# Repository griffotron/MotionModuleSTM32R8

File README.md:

# Introduction 
This repository contains the PCB design files and source code for the STM32 based Motion Module used in my Mechanical Display.

The Motion Module uses an STM32F103R8 microcontroller to run 14 Trinamic TMC2209 stepper drivers. It recieves motor movement commands via CAN Bus from the ESP32 based Motion Controller. Please see the related repos for the [ESP32 Controller](https://github.com/griffotron/MotionControllerESP32) and [CAD Designs](https://github.com/griffotron/MechanicalDisplayCAD).

# Build Video
Click below to watch the full build video on YouTube

# Getting Started

## PCB
You'll need at least KiCad 8 to view and modify the PCB design files. The `PCB/production` folder contains files suitable for production with JLC PCB, including a zip containing the Gerbers for fabrication and `bom.csv` and `positions.csv` for SMT assembly. The `bom.csv` uses components from LCSC.com. If any components are no longer be available/out of stock you'll need to select an alternative.

## Code
The code uses PlatformIO (I used the VSCode plugin) and the Arduino framework.

CAN Bus library is from https://github.com/pazi88/CANBus

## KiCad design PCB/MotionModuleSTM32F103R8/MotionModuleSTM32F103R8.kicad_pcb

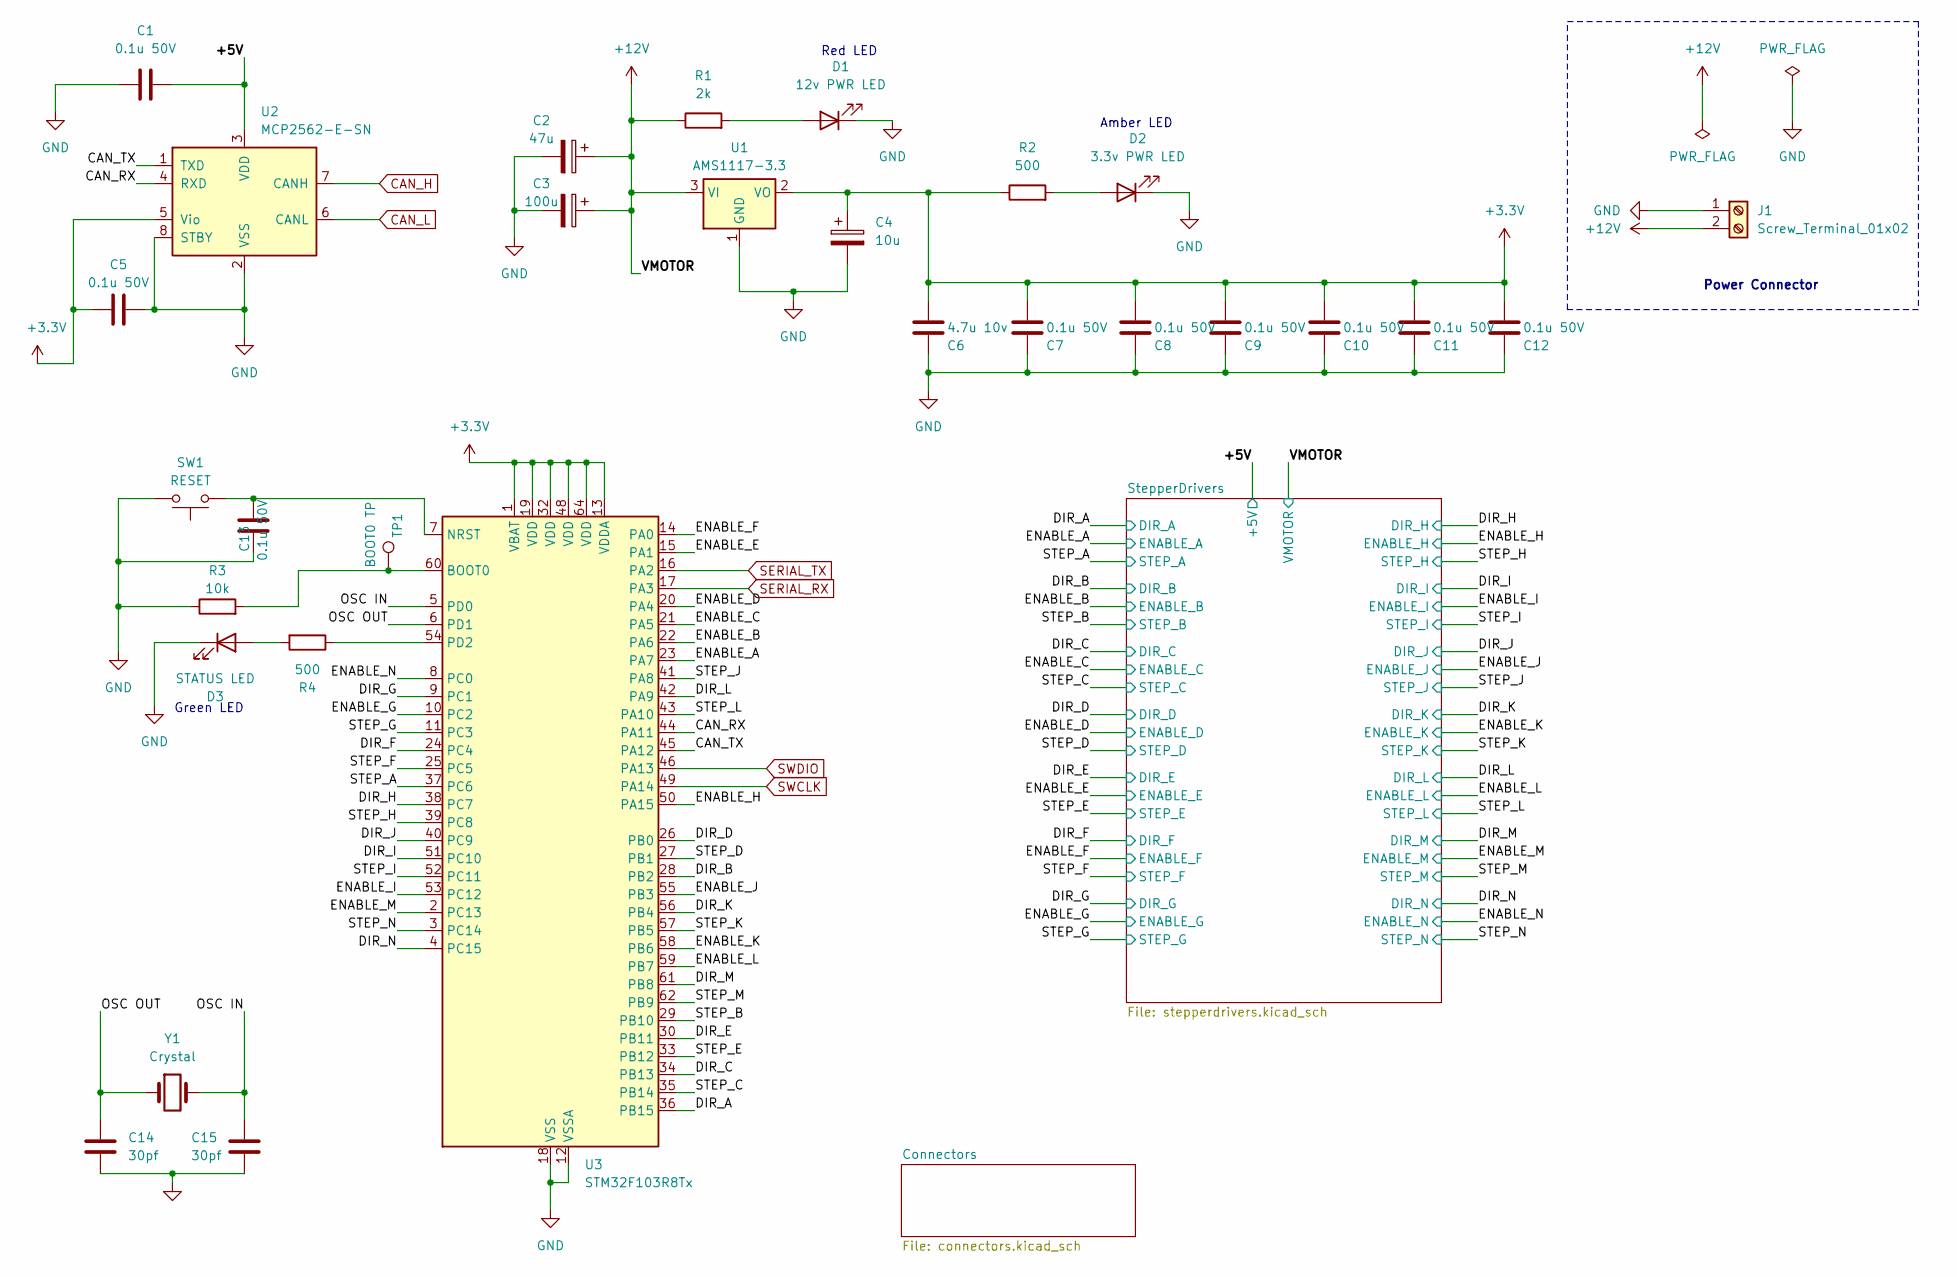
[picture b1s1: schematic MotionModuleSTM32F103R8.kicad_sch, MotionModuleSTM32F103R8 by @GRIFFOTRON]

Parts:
C1, C5, C7, C8, C9, C10, C11, C12, C13: 0.1u 50V; C_0603_1608Metric; MPN CC0603KRX7R9BB104; LCSC C14663
C2: 47u; CP_Elec_5x5.4; MPN RST47UF25V035; LCSC C4747958
C3: 100u; CP_Elec_6.3x4.9; MPN SPT1EM101E05TRVZC; LCSC C22395169
C4: 10u; CP_Elec_4x5.7; MPN FZ10UF25V90RV0144; DigiKey 732-6401-1-ND (Poly)
C6: 4.7u 10v; C_0603_1608Metric; MPN CL10A475KO8NNNC; LCSC C19666
C14, C15: 30pf; C_0603_1608Metric; MPN 0603CG300J500NT; LCSC C1658
D1: 12v PWR LED; LED_0603_1608Metric; MPN A-SP192YR6C-A02-4T; DigiKey 732-4978-1-ND
D2: 3.3v PWR LED; LED_0603_1608Metric; MPN A-SP192GS1C-A01-4T; DigiKey 732-150060AS75000CT-ND
D3: STATUS LED; LED_0603_1608Metric; MPN A-SP192DGHC-C01-4T; DigiKey 732-4971-1-ND
J1: Screw_Terminal_01x02; PinHeader_1x02_P2.54mm_Vertical
R1: 2k; R_0603_1608Metric; MPN 0603WAF2001T5E; LCSC C22975
R2, R4: 500; R_0603_1608Metric; MPN 0603WAF5100T5E; LCSC C23193
R3: 10k; R_0603_1608Metric; MPN 0603WAF1002T5E; LCSC C25804
SW1: RESET; SW_Tactile_SPST_NO_Straight_CK_PTS636Sx25SMTRLFS; MPN PTS636SK25SMTRLFS; LCSC C2689642
TP1: BOOT0 TP; TestPoint_Pad_D2.0mm
U1: AMS1117-3.3; SOT-223-3_TabPin2; MPN AMS1117-3.3; LCSC C5250992
U2: MCP2562-E-SN; SOIC-8_3.9x4.9mm_P1.27mm; MPN MCP2562T-E/SN; LCSC C191417
U3: STM32F103R8Tx; LQFP-64_10x10mm_P0.5mm; MPN STM32F103R8T6; LCSC C46034
Y1: Crystal; Crystal_SMD_5032-2Pin_5.0x3.2mm; MPN X50328MSB2GI; LCSC C115962

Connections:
+3.3V: C4.1, C5.2, C6.1, C7.1, C8.1, C9.1, C10.1, C11.1, C12.1, R2.1, U1.2 (VO), U2.5 (Vio), U3.1 (VBAT), U3.13 (VDDA), U3.19 (VDD), U3.32 (VDD), U3.48 (VDD), U3.64 (VDD)
+12V: C2.1, C3.1, J1.2, R1.1, U1.3 (VI); also elsewhere on the board
/+5V: C1.1, U2.3 (VDD); also elsewhere on the board
/CAN_RX: U2.4 (RXD), U3.44 (PA11)
/CAN_TX: U2.1 (TXD), U3.45 (PA12)
/DIR_A: U3.36 (PB15); also elsewhere on the board
/DIR_B: U3.28 (PB2); also elsewhere on the board
/DIR_C: U3.34 (PB13); also elsewhere on the board
/DIR_D: U3.26 (PB0); also elsewhere on the board
/DIR_E: U3.30 (PB11); also elsewhere on the board
/DIR_F: U3.24 (PC4); also elsewhere on the board
/DIR_G: U3.9 (PC1); also elsewhere on the board
/DIR_H: U3.38 (PC7); also elsewhere on the board
/DIR_I: U3.51 (PC10); also elsewhere on the board
/DIR_J: U3.40 (PC9); also elsewhere on the board
/DIR_K: U3.56 (PB4); also elsewhere on the board
/DIR_L: U3.42 (PA9); also elsewhere on the board
/DIR_M: U3.61 (PB8); also elsewhere on the board
/DIR_N: U3.4 (PC15); also elsewhere on the board
/ENABLE_A: U3.23 (PA7); also elsewhere on the board
/ENABLE_B: U3.22 (PA6); also elsewhere on the board
/ENABLE_C: U3.21 (PA5); also elsewhere on the board
/ENABLE_D: U3.20 (PA4); also elsewhere on the board
/ENABLE_E: U3.15 (PA1); also elsewhere on the board
/ENABLE_F: U3.14 (PA0); also elsewhere on the board
/ENABLE_G: U3.10 (PC2); also elsewhere on the board
/ENABLE_H: U3.50 (PA15); also elsewhere on the board
/ENABLE_I: U3.53 (PC12); also elsewhere on the board
/ENABLE_J: U3.55 (PB3); also elsewhere on the board
/ENABLE_K: U3.58 (PB6); also elsewhere on the board
/ENABLE_L: U3.59 (PB7); also elsewhere on the board
/ENABLE_M: U3.2 (PC13); also elsewhere on the board
/ENABLE_N: U3.8 (PC0); also elsewhere on the board
/OSC IN: C15.1, U3.5 (PD0), Y1.2
/OSC OUT: C14.2, U3.6 (PD1), Y1.1
/STEP_A: U3.37 (PC6); also elsewhere on the board
/STEP_B: U3.29 (PB10); also elsewhere on the board
/STEP_C: U3.35 (PB14); also elsewhere on the board
/STEP_D: U3.27 (PB1); also elsewhere on the board
/STEP_E: U3.33 (PB12); also elsewhere on the board
/STEP_F: U3.25 (PC5); also elsewhere on the board
/STEP_G: U3.11 (PC3); also elsewhere on the board
/STEP_H: U3.39 (PC8); also elsewhere on the board
/STEP_I: U3.52 (PC11); also elsewhere on the board
/STEP_J: U3.41 (PA8); also elsewhere on the board
/STEP_K: U3.57 (PB5); also elsewhere on the board
/STEP_L: U3.43 (PA10); also elsewhere on the board
/STEP_M: U3.62 (PB9); also elsewhere on the board
/STEP_N: U3.3 (PC14); also elsewhere on the board
CAN_H: U2.7 (CANH); also elsewhere on the board
CAN_L: U2.6 (CANL); also elsewhere on the board
GND: C1.2, C2.2, C3.2, C4.2, C5.1, C6.2, C7.2, C8.2, C9.2, C10.2, C11.2, C12.2, C13.2, C14.1, C15.2, D1.1 (K), D2.1 (K), D3.1 (K), J1.1, R3.1, SW1.2, U1.1 (GND), U2.2 (VSS), U2.8 (STBY), U3.12 (VSSA), U3.18 (VSS), U3.31 (VSS), U3.47 (VSS), U3.63 (VSS); also elsewhere on the board
unnamed: D1.2 (A), R1.2
unnamed: D2.2 (A), R2.2
unnamed: D3.2 (A), R4.2
unnamed: R3.2, TP1.1, U3.60 (BOOT0)
unnamed: C13.1, SW1.1, U3.7 (NRST)
unnamed: R4.1, U3.54 (PD2)
SERIAL_RX: U3.17 (PA3); also elsewhere on the board
SERIAL_TX: U3.16 (PA2); also elsewhere on the board
SWCLK: U3.49 (PA14); also elsewhere on the board
SWDIO: U3.46 (PA13); also elsewhere on the board

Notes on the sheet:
Green LED
Power Connector
Amber LED
Red LED

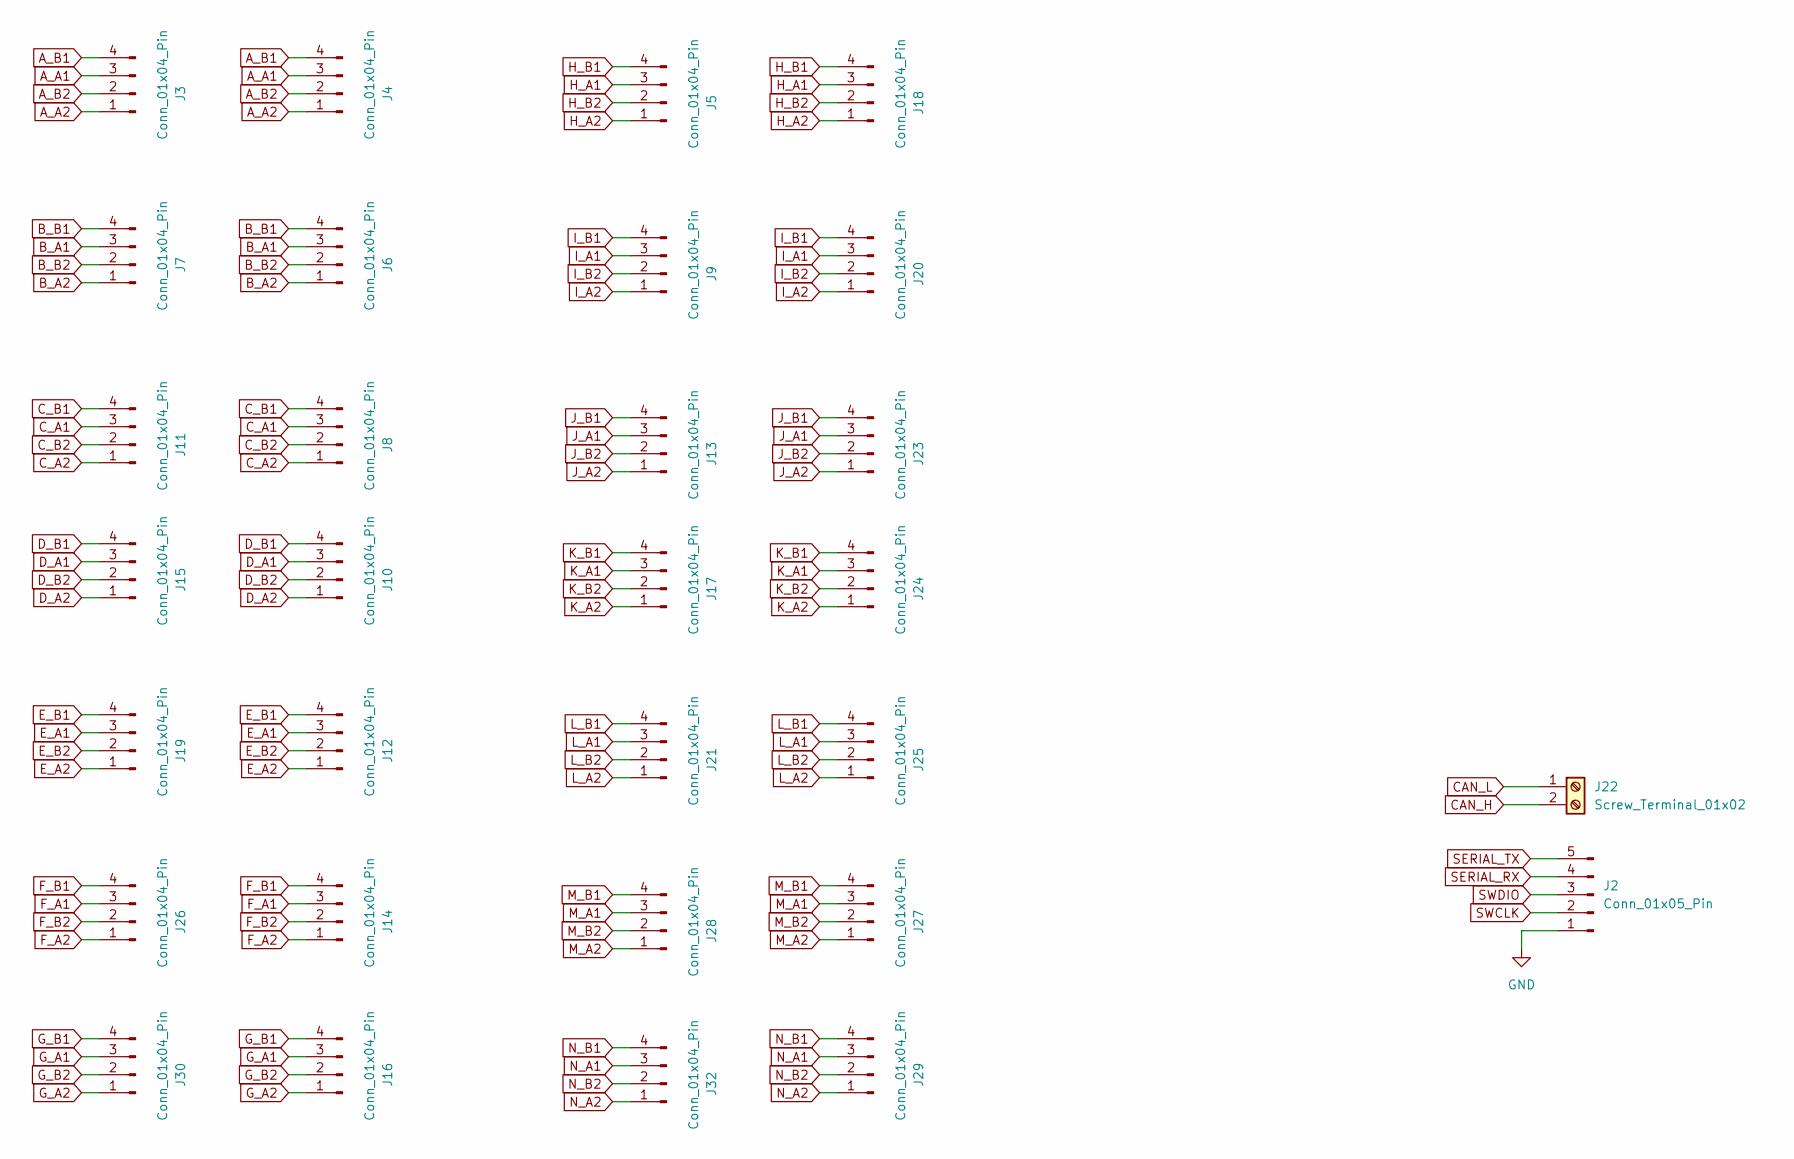
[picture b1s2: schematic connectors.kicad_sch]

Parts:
J2: Conn_01x05_Pin; PinHeader_1x05_P2.54mm_Vertical
J3, J5, J7, J9, J11, J13, J15, J17, J19, J21, J26, J28, J30, J32: Conn_01x04_Pin; JST_PH_B4B-PH-K_1x04_P2.00mm_Vertical; MPN B4B-PH-K-S(LF)(SN); LCSC C131334
J4, J6, J8, J10, J12, J14, J16, J18, J20, J23, J24, J25, J27, J29: Conn_01x04_Pin; PinHeader_1x04_P2.54mm_Vertical
J22: Screw_Terminal_01x02; PinHeader_1x02_P2.54mm_Vertical

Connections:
A_A1: J3.3, J4.3; also elsewhere on the board
A_A2: J3.1, J4.1; also elsewhere on the board
A_B1: J3.4, J4.4; also elsewhere on the board
A_B2: J3.2, J4.2; also elsewhere on the board
B_A1: J6.3, J7.3; also elsewhere on the board
B_A2: J6.1, J7.1; also elsewhere on the board
B_B1: J6.4, J7.4; also elsewhere on the board
B_B2: J6.2, J7.2; also elsewhere on the board
CAN_H: J22.2; also elsewhere on the board
CAN_L: J22.1; also elsewhere on the board
C_A1: J8.3, J11.3; also elsewhere on the board
C_A2: J8.1, J11.1; also elsewhere on the board
C_B1: J8.4, J11.4; also elsewhere on the board
C_B2: J8.2, J11.2; also elsewhere on the board
D_A1: J10.3, J15.3; also elsewhere on the board
D_A2: J10.1, J15.1; also elsewhere on the board
D_B1: J10.4, J15.4; also elsewhere on the board
D_B2: J10.2, J15.2; also elsewhere on the board
E_A1: J12.3, J19.3; also elsewhere on the board
E_A2: J12.1, J19.1; also elsewhere on the board
E_B1: J12.4, J19.4; also elsewhere on the board
E_B2: J12.2, J19.2; also elsewhere on the board
F_A1: J14.3, J26.3; also elsewhere on the board
F_A2: J14.1, J26.1; also elsewhere on the board
F_B1: J14.4, J26.4; also elsewhere on the board
F_B2: J14.2, J26.2; also elsewhere on the board
GND: J2.1; also elsewhere on the board
G_A1: J16.3, J30.3; also elsewhere on the board
G_A2: J16.1, J30.1; also elsewhere on the board
G_B1: J16.4, J30.4; also elsewhere on the board
G_B2: J16.2, J30.2; also elsewhere on the board
H_A1: J5.3, J18.3; also elsewhere on the board
H_A2: J5.1, J18.1; also elsewhere on the board
H_B1: J5.4, J18.4; also elsewhere on the board
H_B2: J5.2, J18.2; also elsewhere on the board
I_A1: J9.3, J20.3; also elsewhere on the board
I_A2: J9.1, J20.1; also elsewhere on the board
I_B1: J9.4, J20.4; also elsewhere on the board
I_B2: J9.2, J20.2; also elsewhere on the board
J_A1: J13.3, J23.3; also elsewhere on the board
J_A2: J13.1, J23.1; also elsewhere on the board
J_B1: J13.4, J23.4; also elsewhere on the board
J_B2: J13.2, J23.2; also elsewhere on the board
K_A1: J17.3, J24.3; also elsewhere on the board
K_A2: J17.1, J24.1; also elsewhere on the board
K_B1: J17.4, J24.4; also elsewhere on the board
K_B2: J17.2, J24.2; also elsewhere on the board
L_A1: J21.3, J25.3; also elsewhere on the board
L_A2: J21.1, J25.1; also elsewhere on the board
L_B1: J21.4, J25.4; also elsewhere on the board
L_B2: J21.2, J25.2; also elsewhere on the board
M_A1: J27.3, J28.3; also elsewhere on the board
M_A2: J27.1, J28.1; also elsewhere on the board
M_B1: J27.4, J28.4; also elsewhere on the board
M_B2: J27.2, J28.2; also elsewhere on the board
N_A1: J29.3, J32.3; also elsewhere on the board
N_A2: J29.1, J32.1; also elsewhere on the board
N_B1: J29.4, J32.4; also elsewhere on the board
N_B2: J29.2, J32.2; also elsewhere on the board
SERIAL_RX: J2.4; also elsewhere on the board
SERIAL_TX: J2.5; also elsewhere on the board
SWCLK: J2.2; also elsewhere on the board
SWDIO: J2.3; also elsewhere on the board

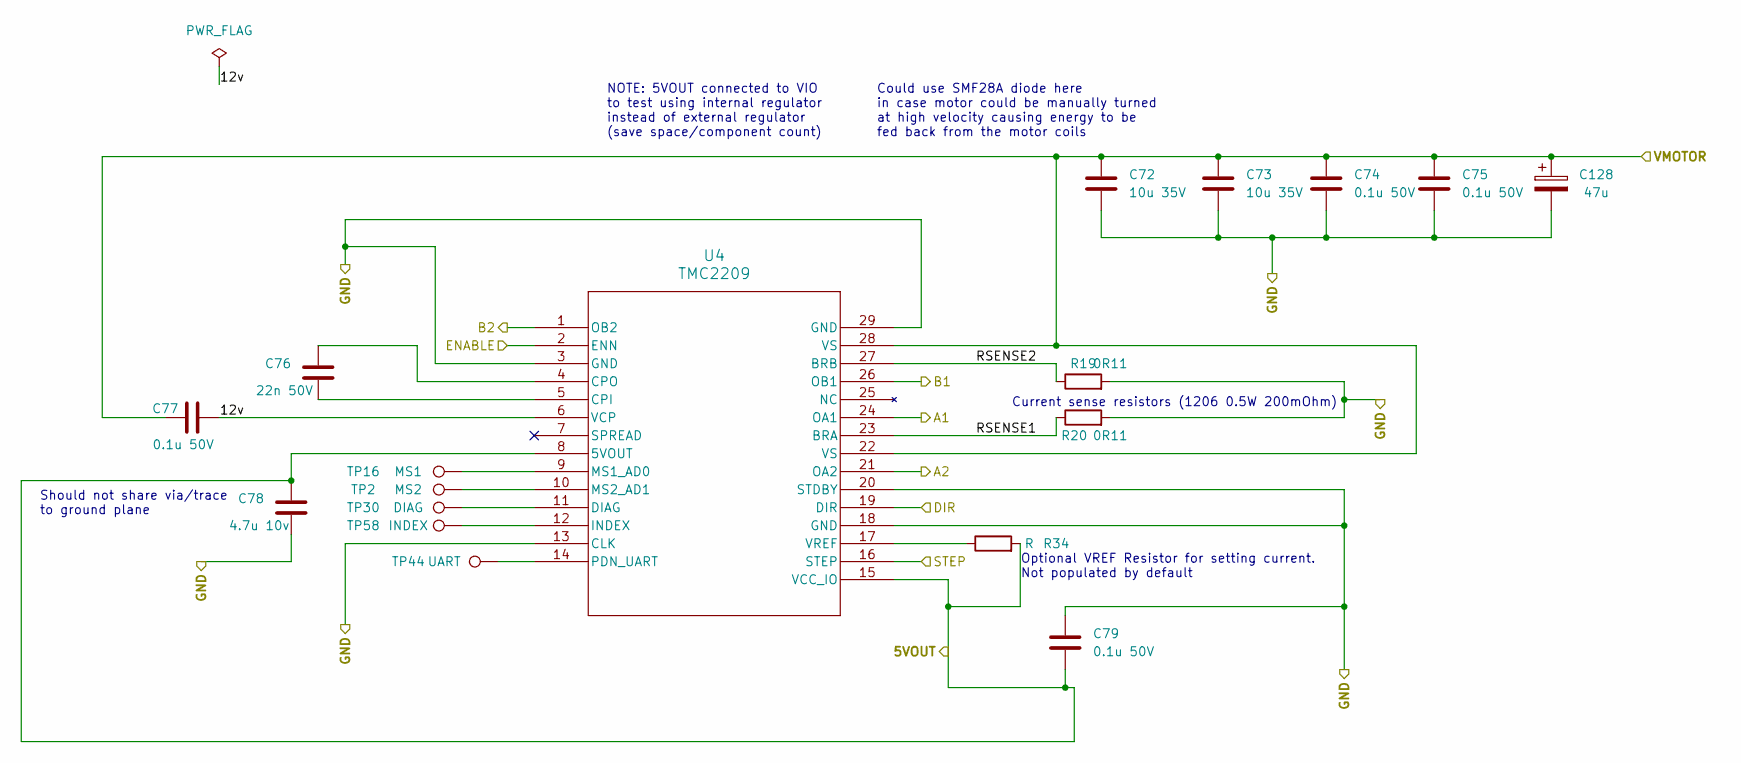
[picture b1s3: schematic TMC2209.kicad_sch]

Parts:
C72, C73: 10u 35V; C_0603_1608Metric; MPN CL10A106MA8NRNC; LCSC C96446
C74, C75, C77, C79: 0.1u 50V; C_0603_1608Metric; MPN CC0603KRX7R9BB104; LCSC C14663
C76: 22n 50V; C_0603_1608Metric; MPN CL10B223KB8NNNC; LCSC C21122
C78: 4.7u 10v; C_0603_1608Metric; MPN CL10A475KO8NNNC; LCSC C19666
C128: 47u; CP_Elec_5x5.4; MPN RST47UF25V035; LCSC C4747958
R19, R20: 0R11; R_1206_3216Metric; MPN PT1206FR-7W0R2L; DigiKey P19309CT-ND (Panasonic 0805)
R34: R; R_0603_1608Metric_Pad0.98x0.95mm_HandSolder
TP2: MS2; TestPoint_Pad_D2.0mm
TP16: MS1; TestPoint_Pad_D2.0mm
TP30: DIAG; TestPoint_Pad_D2.0mm
TP44: UART; TestPoint_Pad_D2.0mm
TP58: INDEX; TestPoint_Pad_D2.0mm
U4: TMC2209; QFN28_5X5_TRI; MPN TMC2209-LA-T; LCSC C465949

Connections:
+12V: C72.1, C73.1, C74.1, C75.1, C77.2, C128.1, U4.22 (VS), U4.28 (VS); also elsewhere on the board
/DIR_A: U4.19 (DIR); also elsewhere on the board
/ENABLE_A: U4.2 (ENN); also elsewhere on the board
/STEP_A: U4.16 (STEP); also elsewhere on the board
A_A1: U4.24 (OA1); also elsewhere on the board
A_A2: U4.21 (OA2); also elsewhere on the board
A_B1: U4.26 (OB1); also elsewhere on the board
A_B2: U4.1 (OB2); also elsewhere on the board
GND: C72.2, C73.2, C74.2, C75.2, C78.2, C79.2, C128.2, R19.2, R20.2, U4.3 (GND), U4.13 (CLK), U4.18 (GND), U4.20 (STDBY), U4.29 (GND); also elsewhere on the board
unnamed: TP30.1, U4.11 (DIAG)
unnamed: TP58.1, U4.12 (INDEX)
unnamed: TP16.1, U4.9 (MS1_AD0)
unnamed: TP2.1, U4.10 (MS2_AD1)
unnamed: TP44.1, U4.14 (PDN_UART)

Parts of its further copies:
C16, C17, C24, C25, C32, C33, C40, C41, C48, C49, C56, C57, C64, C65, C80, C81, C88, C89, C96, C97, C104, C105, C112, C113, C120, C121: 10u 35V; C_0603_1608Metric; MPN CL10A106MA8NRNC; LCSC C96446
C18, C19, C21, C23, C26, C27, C29, C31, C34, C35, C37, C39, C42, C43, C45, C47, C50, C51, C53, C55, C58, C59, C61, C63, C66, C67, C69, C71, C82, C83, C85, C87, C90, C91, C93, C95, C98, C99, C101, C103, C106, C107, C109, C111, C114, C115, C117, C119, C122, C123, C125, C127: 0.1u 50V; C_0603_1608Metric; MPN CC0603KRX7R9BB104; LCSC C14663
C20, C28, C36, C44, C52, C60, C68, C84, C92, C100, C108, C116, C124: 22n 50V; C_0603_1608Metric; MPN CL10B223KB8NNNC; LCSC C21122
C22, C30, C38, C46, C54, C62, C70, C86, C94, C102, C110, C118, C126: 4.7u 10v; C_0603_1608Metric; MPN CL10A475KO8NNNC; LCSC C19666
C129, C130, C131, C132, C133, C134, C135, C136, C137, C138, C139, C140, C141: 47u; CP_Elec_5x5.4; MPN RST47UF25V035; LCSC C4747958
R5, R6, R7, R8, R9, R10, R11, R12, R13, R14, R15, R16, R17, R18, R21, R22, R23, R24, R25, R26, R27, R28, R29, R30, R31, R32: 0R11; R_1206_3216Metric; MPN PT1206FR-7W0R2L; DigiKey P19309CT-ND (Panasonic 0805)
R33, R35, R36, R37, R38, R39, R40, R41, R42, R43, R44, R45, R46: R; R_0603_1608Metric_Pad0.98x0.95mm_HandSolder
U5, U6, U7, U8, U9, U10, U11, U12, U13, U14, U15, U16, U17: TMC2209; QFN28_5X5_TRI; MPN TMC2209-LA-T; LCSC C465949

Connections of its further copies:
+12V: C16.1, C17.1, C18.1, C19.1, C21.2, C24.1, C25.1, C26.1, C27.1, C29.2, C32.1, C33.1, C34.1, C35.1, C37.2, C40.1, C41.1, C42.1, C43.1, C45.2, C48.1, C49.1, C50.1, C51.1, C53.2, C56.1, C57.1, C58.1, C59.1, C61.2, C64.1, C65.1, C66.1, C67.1, C69.2, C80.1, C81.1, C82.1, C83.1, C85.2, C88.1, C89.1, C90.1, C91.1, C93.2, C96.1, C97.1, C98.1, C99.1, C101.2, C104.1, C105.1, C106.1, C107.1, C109.2, C112.1, C113.1, C114.1, C115.1, C117.2, C120.1, C121.1, C122.1, C123.1, C125.2, C129.1, C130.1, C131.1, C132.1, C133.1, C134.1, C135.1, C136.1, C137.1, C138.1, C139.1, C140.1, C141.1, U5.22 (VS), U5.28 (VS), U6.22 (VS), U6.28 (VS), U7.22 (VS), U7.28 (VS), U8.22 (VS), U8.28 (VS), U9.22 (VS), U9.28 (VS), U10.22 (VS), U10.28 (VS), U11.22 (VS), U11.28 (VS), U12.22 (VS), U12.28 (VS), U13.22 (VS), U13.28 (VS), U14.22 (VS), U14.28 (VS), U15.22 (VS), U15.28 (VS), U16.22 (VS), U16.28 (VS), U17.22 (VS), U17.28 (VS); also elsewhere on the board
/+5V: C126.1, C127.1, R46.2, U17.8 (5VOUT), U17.15 (VCC_IO); also elsewhere on the board
/DIR_B: U8.19 (DIR); also elsewhere on the board
/DIR_C: U9.19 (DIR); also elsewhere on the board
/DIR_D: U5.19 (DIR); also elsewhere on the board
/DIR_E: U10.19 (DIR); also elsewhere on the board
/DIR_F: U7.19 (DIR); also elsewhere on the board
/DIR_G: U6.19 (DIR); also elsewhere on the board
/DIR_H: U11.19 (DIR); also elsewhere on the board
/DIR_I: U12.19 (DIR); also elsewhere on the board
/DIR_J: U13.19 (DIR); also elsewhere on the board
/DIR_K: U14.19 (DIR); also elsewhere on the board
/DIR_L: U15.19 (DIR); also elsewhere on the board
/DIR_M: U16.19 (DIR); also elsewhere on the board
/DIR_N: U17.19 (DIR); also elsewhere on the board
/ENABLE_B: U8.2 (ENN); also elsewhere on the board
/ENABLE_C: U9.2 (ENN); also elsewhere on the board
/ENABLE_D: U5.2 (ENN); also elsewhere on the board
/ENABLE_E: U10.2 (ENN); also elsewhere on the board
/ENABLE_F: U7.2 (ENN); also elsewhere on the board
/ENABLE_G: U6.2 (ENN); also elsewhere on the board
/ENABLE_H: U11.2 (ENN); also elsewhere on the board
/ENABLE_I: U12.2 (ENN); also elsewhere on the board
/ENABLE_J: U13.2 (ENN); also elsewhere on the board
/ENABLE_K: U14.2 (ENN); also elsewhere on the board
/ENABLE_L: U15.2 (ENN); also elsewhere on the board
/ENABLE_M: U16.2 (ENN); also elsewhere on the board
/ENABLE_N: U17.2 (ENN); also elsewhere on the board
/STEP_B: U8.16 (STEP); also elsewhere on the board
/STEP_C: U9.16 (STEP); also elsewhere on the board
/STEP_D: U5.16 (STEP); also elsewhere on the board
/STEP_E: U10.16 (STEP); also elsewhere on the board
/STEP_F: U7.16 (STEP); also elsewhere on the board
/STEP_G: U6.16 (STEP); also elsewhere on the board
/STEP_H: U11.16 (STEP); also elsewhere on the board
/STEP_I: U12.16 (STEP); also elsewhere on the board
/STEP_J: U13.16 (STEP); also elsewhere on the board
/STEP_K: U14.16 (STEP); also elsewhere on the board
/STEP_L: U15.16 (STEP); also elsewhere on the board
/STEP_M: U16.16 (STEP); also elsewhere on the board
/STEP_N: U17.16 (STEP); also elsewhere on the board
/StepperDrivers/TMC2209-B/5VOUT: C54.1, C55.1, R37.2, U8.8 (5VOUT), U8.15 (VCC_IO)
/StepperDrivers/TMC2209-B/12v: C53.1, U8.6 (VCP)
/StepperDrivers/TMC2209-B/RSENSE1: R14.1, U8.23 (BRA)
/StepperDrivers/TMC2209-B/RSENSE2: R13.1, U8.27 (BRB)
/StepperDrivers/TMC2209-C/5VOUT: C62.1, C63.1, R38.2, U9.8 (5VOUT), U9.15 (VCC_IO)
/StepperDrivers/TMC2209-C/12v: C61.1, U9.6 (VCP)
/StepperDrivers/TMC2209-C/RSENSE1: R16.1, U9.23 (BRA)
/StepperDrivers/TMC2209-C/RSENSE2: R15.1, U9.27 (BRB)
/StepperDrivers/TMC2209-D/12v: C29.1, U5.6 (VCP)
/StepperDrivers/TMC2209-D/RSENSE1: R8.1, U5.23 (BRA)
/StepperDrivers/TMC2209-D/RSENSE2: R7.1, U5.27 (BRB)
/StepperDrivers/TMC2209-E/5VOUT: C70.1, C71.1, R39.2, U10.8 (5VOUT), U10.15 (VCC_IO)
/StepperDrivers/TMC2209-E/12v: C69.1, U10.6 (VCP)
/StepperDrivers/TMC2209-E/RSENSE1: R18.1, U10.23 (BRA)
/StepperDrivers/TMC2209-E/RSENSE2: R17.1, U10.27 (BRB)
/StepperDrivers/TMC2209-F/5VOUT: C46.1, C47.1, R36.2, U7.8 (5VOUT), U7.15 (VCC_IO)
/StepperDrivers/TMC2209-F/12v: C45.1, U7.6 (VCP)
/StepperDrivers/TMC2209-F/RSENSE1: R12.1, U7.23 (BRA)
/StepperDrivers/TMC2209-F/RSENSE2: R11.1, U7.27 (BRB)
/StepperDrivers/TMC2209-G/5VOUT: C38.1, C39.1, R35.2, U6.8 (5VOUT), U6.15 (VCC_IO)
/StepperDrivers/TMC2209-G/12v: C37.1, U6.6 (VCP)
/StepperDrivers/TMC2209-G/RSENSE1: R10.1, U6.23 (BRA)
/StepperDrivers/TMC2209-G/RSENSE2: R9.1, U6.27 (BRB)
/StepperDrivers/TMC2209-I/5VOUT: C86.1, C87.1, R41.2, U12.8 (5VOUT), U12.15 (VCC_IO)
/StepperDrivers/TMC2209-I/12v: C85.1, U12.6 (VCP)
/StepperDrivers/TMC2209-I/RSENSE1: R22.1, U12.23 (BRA)
/StepperDrivers/TMC2209-I/RSENSE2: R21.1, U12.27 (BRB)
/StepperDrivers/TMC2209-J/5VOUT: C94.1, C95.1, R42.2, U13.8 (5VOUT), U13.15 (VCC_IO)
/StepperDrivers/TMC2209-J/12v: C93.1, U13.6 (VCP)
/StepperDrivers/TMC2209-J/RSENSE1: R24.1, U13.23 (BRA)
/StepperDrivers/TMC2209-J/RSENSE2: R23.1, U13.27 (BRB)
/StepperDrivers/TMC2209-K/5VOUT: C102.1, C103.1, R43.2, U14.8 (5VOUT), U14.15 (VCC_IO)
/StepperDrivers/TMC2209-K/12v: C101.1, U14.6 (VCP)
/StepperDrivers/TMC2209-K/RSENSE1: R26.1, U14.23 (BRA)
/StepperDrivers/TMC2209-K/RSENSE2: R25.1, U14.27 (BRB)
/StepperDrivers/TMC2209-L/5VOUT: C110.1, C111.1, R44.2, U15.8 (5VOUT), U15.15 (VCC_IO)
/StepperDrivers/TMC2209-L/12v: C109.1, U15.6 (VCP)
/StepperDrivers/TMC2209-L/RSENSE1: R28.1, U15.23 (BRA)
/StepperDrivers/TMC2209-L/RSENSE2: R27.1, U15.27 (BRB)
/StepperDrivers/TMC2209-M/5VOUT: C118.1, C119.1, R45.2, U16.8 (5VOUT), U16.15 (VCC_IO)
/StepperDrivers/TMC2209-M/12v: C117.1, U16.6 (VCP)
/StepperDrivers/TMC2209-M/RSENSE1: R30.1, U16.23 (BRA)
/StepperDrivers/TMC2209-M/RSENSE2: R29.1, U16.27 (BRB)
/StepperDrivers/TMC2209-N/12v: C125.1, U17.6 (VCP)
/StepperDrivers/TMC2209-N/RSENSE1: R32.1, U17.23 (BRA)
/StepperDrivers/TMC2209-N/RSENSE2: R31.1, U17.27 (BRB)
B_A1: U8.24 (OA1); also elsewhere on the board
B_A2: U8.21 (OA2); also elsewhere on the board
B_B1: U8.26 (OB1); also elsewhere on the board
B_B2: U8.1 (OB2); also elsewhere on the board
C_A1: U9.24 (OA1); also elsewhere on the board
C_A2: U9.21 (OA2); also elsewhere on the board
C_B1: U9.26 (OB1); also elsewhere on the board
C_B2: U9.1 (OB2); also elsewhere on the board
D_A1: U5.24 (OA1); also elsewhere on the board
D_A2: U5.21 (OA2); also elsewhere on the board
D_B1: U5.26 (OB1); also elsewhere on the board
D_B2: U5.1 (OB2); also elsewhere on the board
E_A1: U10.24 (OA1); also elsewhere on the board
E_A2: U10.21 (OA2); also elsewhere on the board
E_B1: U10.26 (OB1); also elsewhere on the board
E_B2: U10.1 (OB2); also elsewhere on the board
F_A1: U7.24 (OA1); also elsewhere on the board
F_A2: U7.21 (OA2); also elsewhere on the board
F_B1: U7.26 (OB1); also elsewhere on the board
F_B2: U7.1 (OB2); also elsewhere on the board
GND: C16.2, C17.2, C18.2, C19.2, C22.2, C23.2, C24.2, C25.2, C26.2, C27.2, C30.2, C31.2, C32.2, C33.2, C34.2, C35.2, C38.2, C39.2, C40.2, C41.2, C42.2, C43.2, C46.2, C47.2, C48.2, C49.2, C50.2, C51.2, C54.2, C55.2, C56.2, C57.2, C58.2, C59.2, C62.2, C63.2, C64.2, C65.2, C66.2, C67.2, C70.2, C71.2, C80.2, C81.2, C82.2, C83.2, C86.2, C87.2, C88.2, C89.2, C90.2, C91.2, C94.2, C95.2, C96.2, C97.2, C98.2, C99.2, C102.2, C103.2, C104.2, C105.2, C106.2, C107.2, C110.2, C111.2, C112.2, C113.2, C114.2, C115.2, C118.2, C119.2, C120.2, C121.2, C122.2, C123.2, C126.2, C127.2, C129.2, C130.2, C131.2, C132.2, C133.2, C134.2, C135.2, C136.2, C137.2, C138.2, C139.2, C140.2, C141.2, R5.2, R6.2, R7.2, R8.2, R9.2, R10.2, R11.2, R12.2, R13.2, R14.2, R15.2, R16.2, R17.2, R18.2, R21.2, R22.2, R23.2, R24.2, R25.2, R26.2, R27.2, R28.2, R29.2, R30.2, R31.2, R32.2, U5.3 (GND), U5.13 (CLK), U5.18 (GND), U5.20 (STDBY), U5.29 (GND), U6.3 (GND), U6.13 (CLK), U6.18 (GND), U6.20 (STDBY), U6.29 (GND), U7.3 (GND), U7.13 (CLK), U7.18 (GND), U7.20 (STDBY), U7.29 (GND), U8.3 (GND), U8.13 (CLK), U8.18 (GND), U8.20 (STDBY), U8.29 (GND), U9.3 (GND), U9.13 (CLK), U9.18 (GND), U9.20 (STDBY), U9.29 (GND), U10.3 (GND), U10.13 (CLK), U10.18 (GND), U10.20 (STDBY), U10.29 (GND), U11.3 (GND), U11.13 (CLK), U11.18 (GND), U11.20 (STDBY), U11.29 (GND), U12.3 (GND), U12.13 (CLK), U12.18 (GND), U12.20 (STDBY), U12.29 (GND), U13.3 (GND), U13.13 (CLK), U13.18 (GND), U13.20 (STDBY), U13.29 (GND), U14.3 (GND), U14.13 (CLK), U14.18 (GND), U14.20 (STDBY), U14.29 (GND), U15.3 (GND), U15.13 (CLK), U15.18 (GND), U15.20 (STDBY), U15.29 (GND), U16.3 (GND), U16.13 (CLK), U16.18 (GND), U16.20 (STDBY), U16.29 (GND), U17.3 (GND), U17.13 (CLK), U17.18 (GND), U17.20 (STDBY), U17.29 (GND); also elsewhere on the board
G_A1: U6.24 (OA1); also elsewhere on the board
G_A2: U6.21 (OA2); also elsewhere on the board
G_B1: U6.26 (OB1); also elsewhere on the board
G_B2: U6.1 (OB2); also elsewhere on the board
H_A1: U11.24 (OA1); also elsewhere on the board
H_A2: U11.21 (OA2); also elsewhere on the board
H_B1: U11.26 (OB1); also elsewhere on the board
H_B2: U11.1 (OB2); also elsewhere on the board
I_A1: U12.24 (OA1); also elsewhere on the board
I_A2: U12.21 (OA2); also elsewhere on the board
I_B1: U12.26 (OB1); also elsewhere on the board
I_B2: U12.1 (OB2); also elsewhere on the board
J_A1: U13.24 (OA1); also elsewhere on the board
J_A2: U13.21 (OA2); also elsewhere on the board
J_B1: U13.26 (OB1); also elsewhere on the board
J_B2: U13.1 (OB2); also elsewhere on the board
K_A1: U14.24 (OA1); also elsewhere on the board
K_A2: U14.21 (OA2); also elsewhere on the board
K_B1: U14.26 (OB1); also elsewhere on the board
K_B2: U14.1 (OB2); also elsewhere on the board
L_A1: U15.24 (OA1); also elsewhere on the board
L_A2: U15.21 (OA2); also elsewhere on the board
L_B1: U15.26 (OB1); also elsewhere on the board
L_B2: U15.1 (OB2); also elsewhere on the board
M_A1: U16.24 (OA1); also elsewhere on the board
M_A2: U16.21 (OA2); also elsewhere on the board
M_B1: U16.26 (OB1); also elsewhere on the board
M_B2: U16.1 (OB2); also elsewhere on the board
N_A1: U17.24 (OA1); also elsewhere on the board
N_A2: U17.21 (OA2); also elsewhere on the board
N_B1: U17.26 (OB1); also elsewhere on the board
N_B2: U17.1 (OB2); also elsewhere on the board
unnamed: C28.2, U5.5 (CPI)
unnamed: C28.1, U5.4 (CPO)
unnamed: C36.2, U6.5 (CPI)
unnamed: C36.1, U6.4 (CPO)
unnamed: R35.1, U6.17 (VREF)
unnamed: C44.2, U7.5 (CPI)
unnamed: C44.1, U7.4 (CPO)
unnamed: R36.1, U7.17 (VREF)
unnamed: C52.2, U8.5 (CPI)
unnamed: C52.1, U8.4 (CPO)
unnamed: R37.1, U8.17 (VREF)
unnamed: C60.2, U9.5 (CPI)
unnamed: C60.1, U9.4 (CPO)
unnamed: R38.1, U9.17 (VREF)
unnamed: C68.2, U10.5 (CPI)
unnamed: C68.1, U10.4 (CPO)
unnamed: R39.1, U10.17 (VREF)
unnamed: R40.1, U11.17 (VREF)
unnamed: C84.2, U12.5 (CPI)
unnamed: C84.1, U12.4 (CPO)
unnamed: R41.1, U12.17 (VREF)
unnamed: C92.2, U13.5 (CPI)
unnamed: C92.1, U13.4 (CPO)
unnamed: R42.1, U13.17 (VREF)
unnamed: C100.2, U14.5 (CPI)
unnamed: C100.1, U14.4 (CPO)
unnamed: R43.1, U14.17 (VREF)
unnamed: C108.2, U15.5 (CPI)
unnamed: C108.1, U15.4 (CPO)
unnamed: R44.1, U15.17 (VREF)
unnamed: C116.2, U16.5 (CPI)
unnamed: C116.1, U16.4 (CPO)
unnamed: R45.1, U16.17 (VREF)
unnamed: C124.2, U17.5 (CPI)
unnamed: C124.1, U17.4 (CPO)
unnamed: R46.1, U17.17 (VREF)

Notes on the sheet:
Could use SMF28A diode here in case motor could be manually turned at high velocity causing energy to be fed back from the motor coils
NOTE: 5VOUT connected to VIO to test using internal regulator instead of external regulator (save space/component count)
Current sense resistors (1206 0.5W 200mOhm)
Optional VREF Resistor for setting current. Not populated by default
Should not share via/trace to ground plane

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
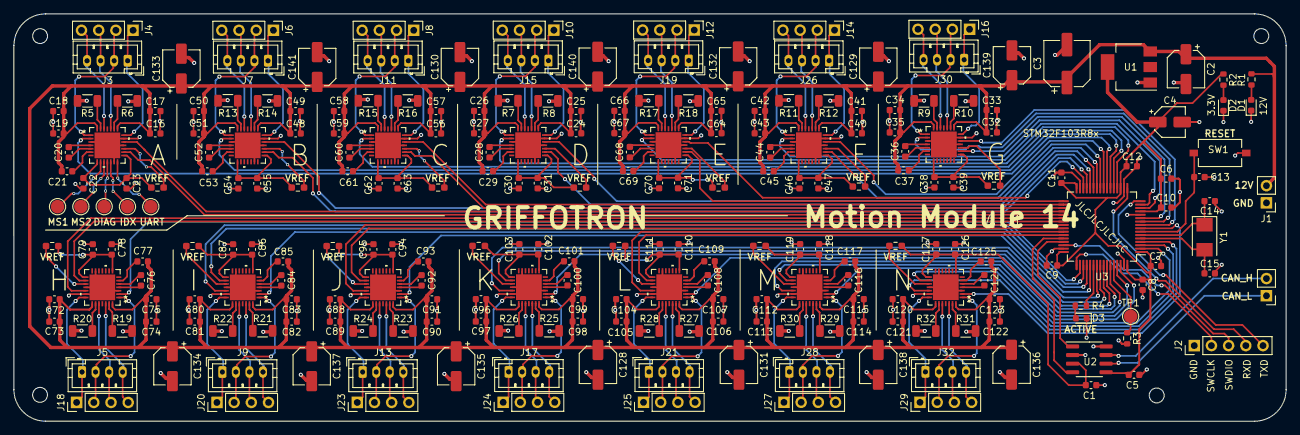
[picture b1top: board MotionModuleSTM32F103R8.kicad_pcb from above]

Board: 4 copper layers, 187.9 x 60.2 mm, 246 parts (0 on the bottom side), 220 nets.

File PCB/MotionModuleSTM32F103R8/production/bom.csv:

Designator,Footprint,Quantity,Value,LCSC Part #
"C1, C10, C101, C103, C106, C107, C109, C11, C111, C114, C115, C117, C119, C12, C122, C123, C125, C127, C13, C18, C19, C21, C23, C26, C27, C29, C31, C34, C35, C37, C39, C42, C43, C45, C47, C5, C50, C51, C53, C55, C58, C59, C61, C63, C66, C67, C69, C7, C71, C74, C75, C77, C79, C8, C82, C83, C85, C87, C9, C90, C91, C93, C95, C98, C99",0603,65,0.1u 50V,C14663
"C100, C108, C116, C124, C20, C28, C36, C44, C52, C60, C68, C76, C84, C92",0603,14,22n 50V,C21122
"C102, C110, C118, C126, C22, C30, C38, C46, C54, C6, C62, C70, C78, C86, C94",0603,15,4.7u 10v,C19666
"C104, C105, C112, C113, C120, C121, C16, C17, C24, C25, C32, C33, C40, C41, C48, C49, C56, C57, C64, C65, C72, C73, C80, C81, C88, C89, C96, C97",0603,28,10u 35V,C96446
"C128, C129, C130, C131, C132, C133, C134, C135, C136, C137, C138, C139, C140, C141, C2",CP_Elec_5x5.4,15,47u,C4747958
"C14, C15",0603,2,30pf,C1658
C3,CP_Elec_6.3x4.9,1,100u,C22395169
C4,CP_Elec_4x5.7,1,10u,C5155338
D1,0603,1,12v PWR LED,C5179611
D2,0603,1,3.3v PWR LED,C5355429
D3,0603,1,STATUS LED,C19171301
"J1, J22",PinHeader_1x02_P2.54mm_Vertical,2,Screw_Terminal_01x02,
"J10, J12, J14, J16, J18, J20, J23, J24, J25, J27, J29, J4, J6, J8",PinHeader_1x04_P2.54mm_Vertical,14,Conn_01x04_Pin,
"J11, J13, J15, J17, J19, J21, J26, J28, J3, J30, J32, J5, J7, J9",JST_PH_B4B-PH-K_1x04_P2.00mm_Vertical,14,Conn_01x04_Pin,C131334
J2,PinHeader_1x05_P2.54mm_Vertical,1,Conn_01x05_Pin,
R1,0603,1,2k,C22975
"R10, R11, R12, R13, R14, R15, R16, R17, R18, R19, R20, R21, R22, R23, R24, R25, R26, R27, R28, R29, R30, R31, R32, R5, R6, R7, R8, R9",1206,28,0R11,C309533
"R2, R4",0603,2,500,C23193
R3,0603,1,10k,C25804
"R33, R34, R35, R36, R37, R38, R39, R40, R41, R42, R43, R44, R45, R46",0603,14,R,
SW1,SW_Tactile_SPST_NO_Straight_CK_PTS636Sx25SMTRLFS,1,RESET,C2689642
TP1,TestPoint_Pad_D2.0mm,1,BOOT0 TP,
TP16,TestPoint_Pad_D2.0mm,1,MS1,
TP2,TestPoint_Pad_D2.0mm,1,MS2,
TP30,TestPoint_Pad_D2.0mm,1,DIAG,
TP44,TestPoint_Pad_D2.0mm,1,UART,
TP58,TestPoint_Pad_D2.0mm,1,INDEX,
U1,SOT-223-3_TabPin2,1,AMS1117-3.3,C5250992
"U10, U11, U12, U13, U14, U15, U16, U17, U4, U5, U6, U7, U8, U9",QFN28_5X5_TRI,14,TMC2209,C465949
U2,SOIC-8_3.9x4.9mm_P1.27mm,1,MCP2562-E-SN,C191417
U3,LQFP-64_10x10mm_P0.5mm,1,STM32F103R8Tx,C46034
Y1,Crystal_SMD_5032-2Pin_5.0x3.2mm,1,Crystal,C115962
